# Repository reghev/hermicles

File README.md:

Hermicles

This is one of my projects for beest, its an esp32-c3-mini-1-n4 going to an LSM6DS3TR Gyroscope with a lithium ion battery, that sits in my suitcase when travelling and connects to my phone over bluetooth and shows me what angle its at so i can see if its flipped over or diagonal or something

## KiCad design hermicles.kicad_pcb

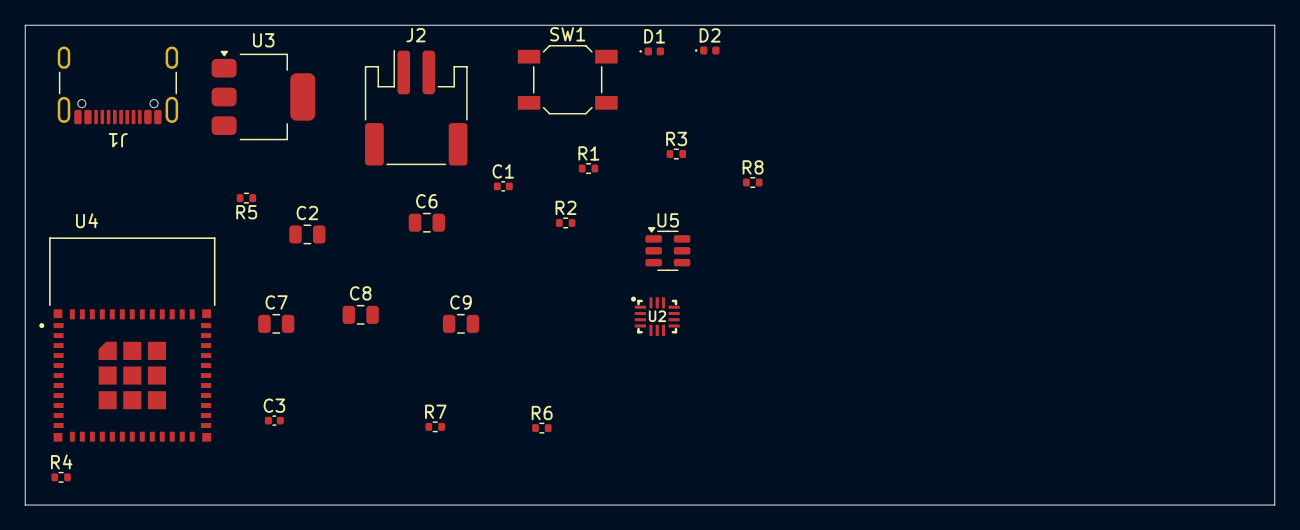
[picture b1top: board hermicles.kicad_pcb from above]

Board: 2 copper layers, 100.1 x 38.4 mm, 24 parts (0 on the bottom side), 17 nets, no tracks yet.

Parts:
C1, C3: 100n; C_0402_1005Metric
C2, C6, C7, C8, C9: 10u; C_0805_2012Metric
D1: CHRG; LED_0402_1005Metric
D2: STDBY; LED_0402_1005Metric
J1: USB_C_Receptacle_USB2.0_14P; USB_C_Receptacle_GCT_USB4105-xx-A_16P_TopMnt_Horizontal
J2: Conn_01x02; JST_PH_S2B-PH-SM4-TB_1x02-1MP_P2.00mm_Horizontal
R1, R2: 4k2; R_0402_1005Metric
R3, R4, R7: 10k; R_0402_1005Metric
R5, R6: 5.1k; R_0402_1005Metric
R8: 1k; R_0402_1005Metric
SW1: SW_Push; SW_SPST_SKQG_WithStem
U2: LSM6DS3TR-C; LGA-14-2.5X3MM
U3: AZ1117-3.3; SOT-223
U4: ESP32-C3-MINI-1-N4; XCVR_ESP32-C3-MINI-1-N4
U5: TP4057; TSOT-23-6

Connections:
+3V3: C1.1, C2.1, C6.1, R1.1, R2.1, R3.1, R4.1, U2.5 (VDDIO), U2.8 (VDD), U2.12 (CS), U3.2 (VO), U4.3 (3V3)
+5V: C9.1, R8.1, U5.4 (V_{CC})
/BAT+: C7.1, C8.1, J2.1, U3.3 (VI), U5.3 (BAT)
/D+: J1.A6 (D+), J1.B6 (D+), U4.27 (IO19)
/D-: J1.A7 (D-), J1.B7 (D-), U4.26 (IO18)
/INT: U2.4 (INT1), U4.13 (IO1)
GND: C1.2, C2.2, C3.2, C6.2, C7.2, C8.2, C9.2, J1.A1 (GND), J1.A12 (GND), J1.B1 (GND), J1.B12 (GND), J1.S1 (SHIELD), J2.2, R5.2, R6.2, R7.2, SW1.1, U2.1 (SDO/SA0), U2.2 (SDX), U2.3 (SCX), U2.6 (GND), U2.7 (GND), U3.1 (GND), U4.1 (GND), U4.2 (GND), U4.11 (GND), U4.14 (GND), U4.36 (GND), U4.37 (GND), U4.38 (GND), U4.39 (GND), U4.40 (GND), U4.41 (GND), U4.42 (GND), U4.43 (GND), U4.44 (GND), U4.45 (GND), U4.46 (GND), U4.47 (GND), U4.48 (GND), U4.49_1 (GND), U4.49_2 (GND), U4.49_3 (GND), U4.49_4 (GND), U4.49_5 (GND), U4.49_6 (GND), U4.49_7 (GND), U4.49_8 (GND), U4.49_9 (GND), U4.50 (GND), U4.51 (GND), U4.52 (GND), U4.53 (GND), U5.2 (GND)
unnamed: D1.2 (A), D2.2 (A), R8.2
unnamed: D1.1 (K), U5.1 (~CHRG)
unnamed: D2.1 (K), U5.5 (STDBY)
unnamed: J1.A5 (CC1), R6.1
unnamed: J1.B5 (CC2), R5.1
unnamed: C3.1, R3.2, SW1.2, U4.8 (EN)
unnamed: R4.2, U4.5 (IO2)
unnamed: R7.1, U5.6 (PROG)
SCL: R2.2, U2.13 (SCL), U4.16 (IO10)
SDA: R1.2, U2.14 (SDA), U4.21 (IO7)

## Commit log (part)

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2026-06-24 readmereadmereadmereadmereadmereadmereadmereadmereadmereadmereadmereadme
    readmereadmereadmereadmereadmereadmereadmereadmereadmereadmereadmereadmereadmereadmereadmereadmereadmereadmereadmereadmereadmereadmereadmereadmereadmereadmereadmereadmereadmereadmereadmereadmereadmer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
